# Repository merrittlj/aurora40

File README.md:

# The Aurora40 Keyboard
- [My blog post](https://merrittlj.github.io/the-aurora40-keyboard/)
- [kbd.news article](https://kbd.news/Aurora40-2716.html)

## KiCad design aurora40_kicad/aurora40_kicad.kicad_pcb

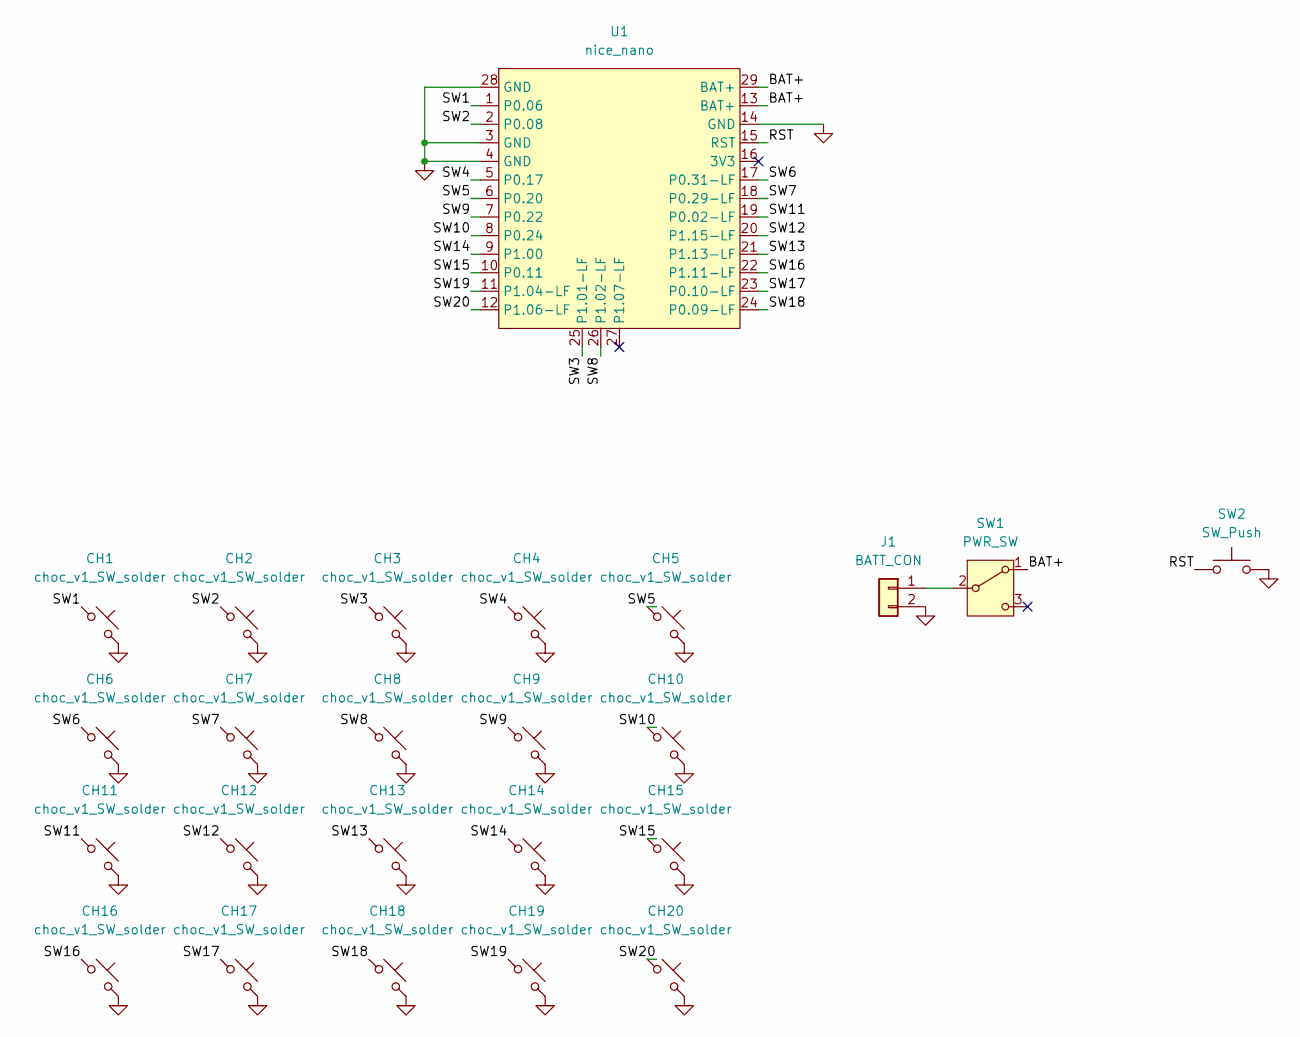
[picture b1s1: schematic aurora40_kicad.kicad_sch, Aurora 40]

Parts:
CH1, CH2, CH3, CH4, CH5, CH6, CH7, CH8, CH9, CH10, CH11, CH12, CH13, CH14, CH15, CH16, CH17, CH18, CH19, CH20: choc_v1_SW_solder; SW_choc_v1_1u
J1: BATT_CON; JST_PH_S2B-PH-K_1x02_P2.00mm_Horizontal
SW1: PWR_SW; SSSS811101
SW2: SW_Push; Panasonic_EVQPUJ_EVQPUA
U1: nice_nano; nice_nano_AH_USBup

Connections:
/BAT+: SW1.1 (A), U1.13 (BAT+), U1.29 (BAT+)
/RST: SW2.1, U1.15 (RST)
/SW1: CH1.1, U1.1 (P0.06)
/SW2: CH2.1, U1.2 (P0.08)
/SW3: CH3.1, U1.25 (P1.01-LF)
/SW4: CH4.1, U1.5 (P0.17)
/SW5: CH5.1, U1.6 (P0.20)
/SW6: CH6.1, U1.17 (P0.31-LF)
/SW7: CH7.1, U1.18 (P0.29-LF)
/SW8: CH8.1, U1.26 (P1.02-LF)
/SW9: CH9.1, U1.7 (P0.22)
/SW10: CH10.1, U1.8 (P0.24)
/SW11: CH11.1, U1.19 (P0.02-LF)
/SW12: CH12.1, U1.20 (P1.15-LF)
/SW13: CH13.1, U1.21 (P1.13-LF)
/SW14: CH14.1, U1.9 (P1.00)
/SW15: CH15.1, U1.10 (P0.11)
/SW16: CH16.1, U1.22 (P1.11-LF)
/SW17: CH17.1, U1.23 (P0.10-LF)
/SW18: CH18.1, U1.24 (P0.09-LF)
/SW19: CH19.1, U1.11 (P1.04-LF)
/SW20: CH20.1, U1.12 (P1.06-LF)
GND: CH1.2, CH2.2, CH3.2, CH4.2, CH5.2, CH6.2, CH7.2, CH8.2, CH9.2, CH10.2, CH11.2, CH12.2, CH13.2, CH14.2, CH15.2, CH16.2, CH17.2, CH18.2, CH19.2, CH20.2, J1.2, SW2.2, U1.3 (GND), U1.4 (GND), U1.14 (GND), U1.28 (GND)
unnamed: J1.1, SW1.2 (B)

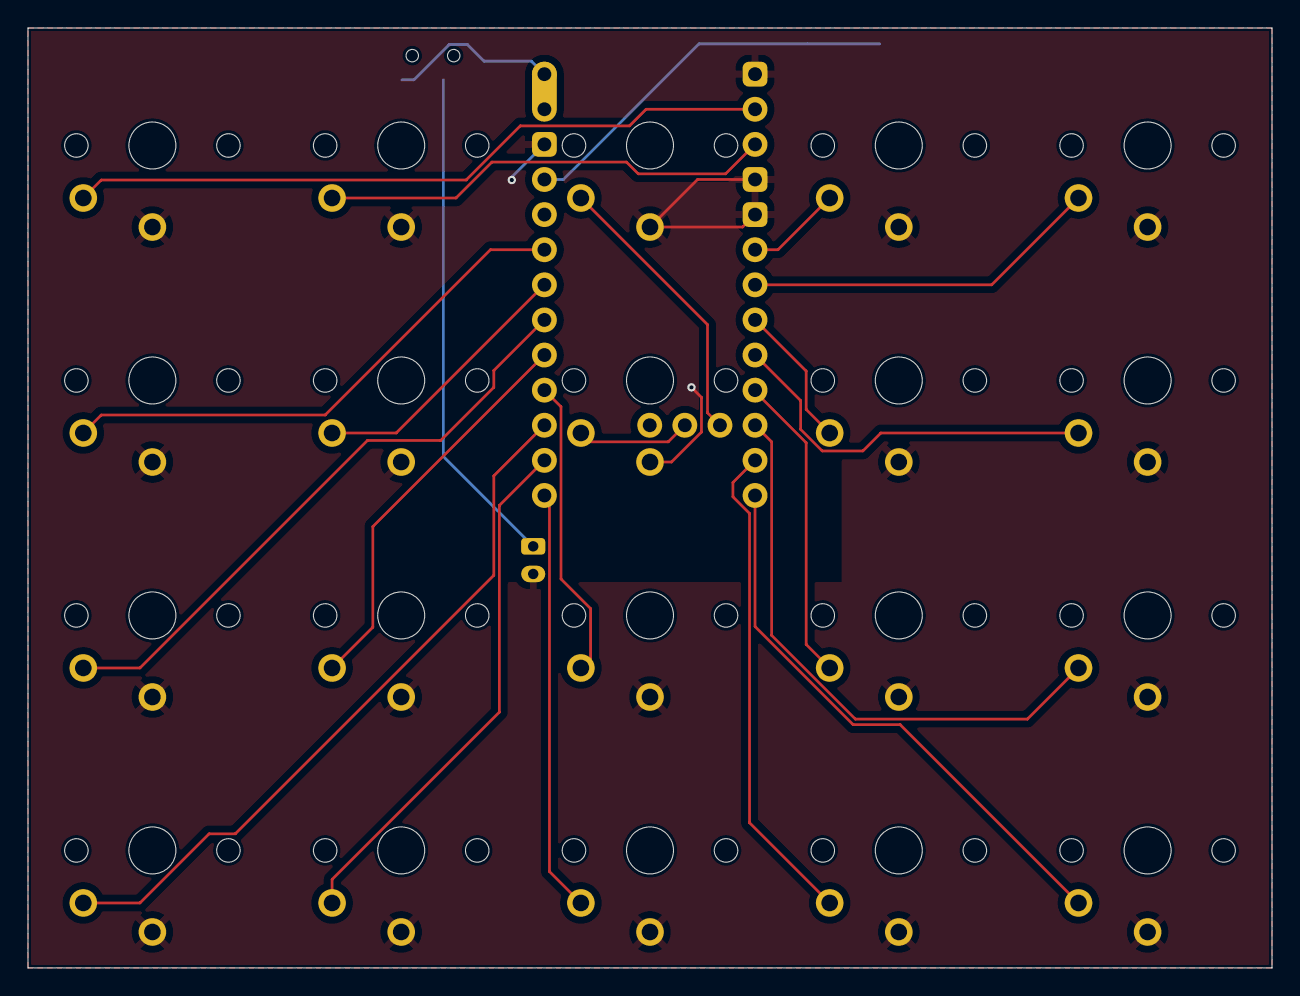
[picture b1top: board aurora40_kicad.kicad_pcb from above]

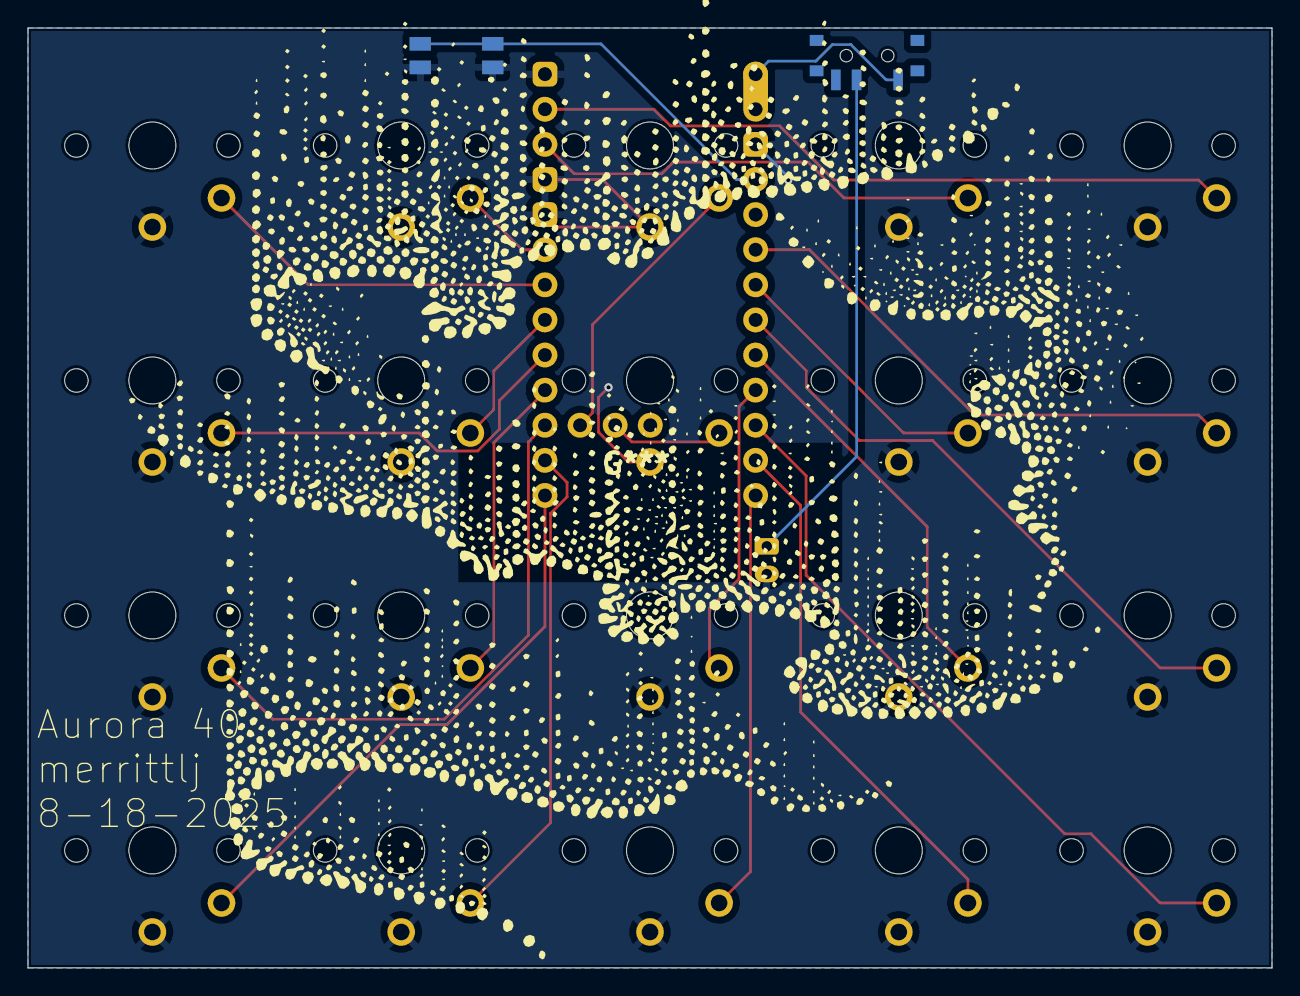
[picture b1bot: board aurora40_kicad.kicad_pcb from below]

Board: 2 copper layers, 90.0 x 68.0 mm, 24 parts (4 on the bottom side), 24 nets.

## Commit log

2025-08-19 initial commit - pcb v1
2025-08-20 add submodules and zmk
2025-08-20 fix submodules
2025-08-21 update zmk submodule
2025-08-22 add case submodule
2025-08-24 update layout
2025-08-27 update case submodule
2025-08-27 update zmk
2025-08-30 update submodules
